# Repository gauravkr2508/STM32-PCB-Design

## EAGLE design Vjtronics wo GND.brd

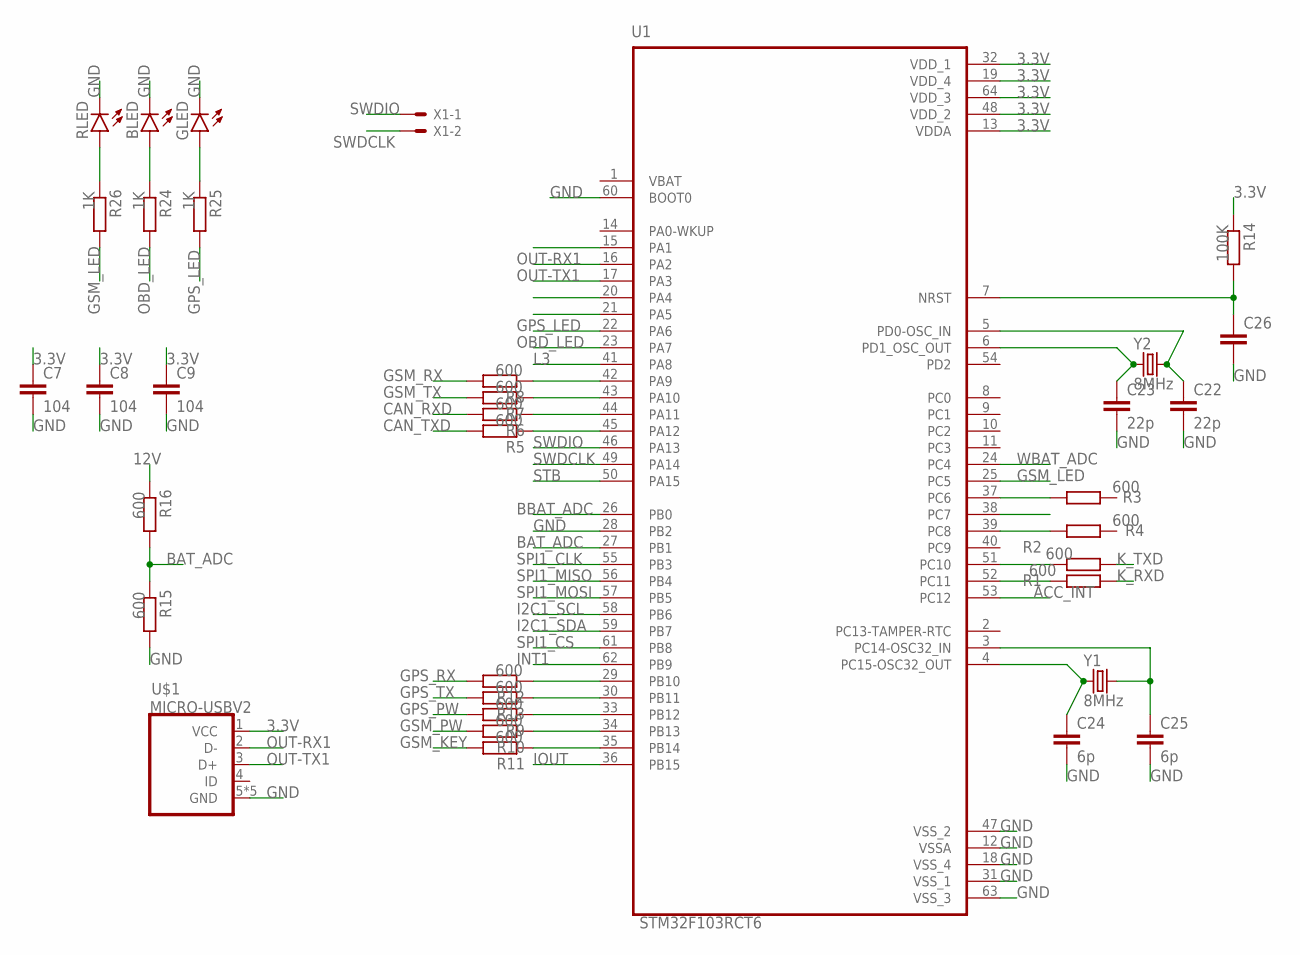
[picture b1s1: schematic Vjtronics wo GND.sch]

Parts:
BLED: LEDCHIPLED_0805; CHIPLED_0805
C7, C8, C9: 104; C0805
C22, C23: 22p; C0805
C24, C25: 6p; C0805
C26: C-EUC0805; C0805
GLED: LEDCHIPLED_0805; CHIPLED_0805
R1, R2, R3, R4, R5, R6, R7, R8, R9, R10, R11, R12, R13, R15, R16: 600; M0805
R14: 100K; M0805
R24, R25, R26: 1K; M0805
RLED: LEDCHIPLED_0805; CHIPLED_0805
U1: STM32F103RCT6; QFP50P1200X1200X160-64N
U$1: MICRO-USBV2; MICRO-USB-2
X1: 22-23-2021
Y1, Y2: 8MHz; CSM-7X-DU

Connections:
3.3V: C7.1, C8.1, C9.1, R14.1, U1.13 (VDDA), U1.19 (VDD_4), U1.32 (VDD_1), U1.48 (VDD_2), U1.64 (VDD_3), U$1.1 (VCC)
12V: R16.1
ACC_INT: U1.53 (PC12)
BAT_ADC: R15.1, R16.2, U1.27 (PB1)
BBAT_ADC: U1.26 (PB0)
CAN_RXD: R6.2
CAN_TXD: R5.2
GND: BLED.C, C7.2, C8.2, C9.2, C22.2, C23.2, C24.2, C25.2, C26.2, GLED.C, R15.2, RLED.C, U1.12 (VSSA), U1.18 (VSS_4), U1.28 (PB2), U1.31 (VSS_1), U1.47 (VSS_2), U1.60 (BOOT0), U1.63 (VSS_3), U$1.5 (GND), U$1.P$1 (GND), U$1.P$2 (GND), U$1.P$3 (GND), U$1.P$4 (GND)
GPS_LED: R25.2, U1.22 (PA6)
GPS_PW: R9.2
GPS_RX: R12.2
GPS_TX: R13.2
GSM_KEY: R11.2
GSM_LED: R26.2, U1.25 (PC5)
GSM_PW: R10.2
GSM_RX: R8.2
GSM_TX: R7.2
I2C1_SCL: U1.58 (PB6)
I2C1_SDA: U1.59 (PB7)
INT1: U1.62 (PB9)
IOUT: U1.36 (PB15)
K_RXD: R1.1
K_TXD: R2.1
L3: U1.41 (PA8)
unnamed: R13.1, U1.30 (PB11)
unnamed: R5.1, U1.45 (PA12)
unnamed: R6.1, U1.44 (PA11)
unnamed: R7.1, U1.43 (PA10)
unnamed: R8.1, U1.42 (PA9)
unnamed: R1.2, U1.52 (PC11)
unnamed: R2.2, U1.51 (PC10)
unnamed: R12.1, U1.29 (PB10)
unnamed: R4.2, U1.39 (PC8)
unnamed: R3.2, U1.37 (PC6)
unnamed: R11.1, U1.35 (PB14)
unnamed: R10.1, U1.34 (PB13)
unnamed: R9.1, U1.33 (PB12)
unnamed: C23.1, U1.6 (PD1_OSC_OUT), Y2.1
unnamed: C26.1, R14.2, U1.7 (NRST)
unnamed: C22.1, U1.5 (PD0-OSC_IN), Y2.2
unnamed: C24.1, U1.4 (PC15-OSC32_OUT), Y1.1
unnamed: C25.1, U1.3 (PC14-OSC32_IN), Y1.2
unnamed: R26.1, RLED.A
unnamed: BLED.A, R24.1
unnamed: GLED.A, R25.1
OBD_LED: R24.2, U1.23 (PA7)
OUT-RX1: U1.16 (PA2), U$1.2 (D-)
OUT-TX1: U1.17 (PA3), U$1.3 (D+)
SPI1_CLK: U1.55 (PB3)
SPI1_CS: U1.61 (PB8)
SPI1_MISO: U1.56 (PB4)
SPI1_MOSI: U1.57 (PB5)
STB: U1.50 (PA15)
SWDCLK: U1.49 (PA14), X1.2
SWDIO: U1.46 (PA13), X1.1
WBAT_ADC: U1.24 (PC4)

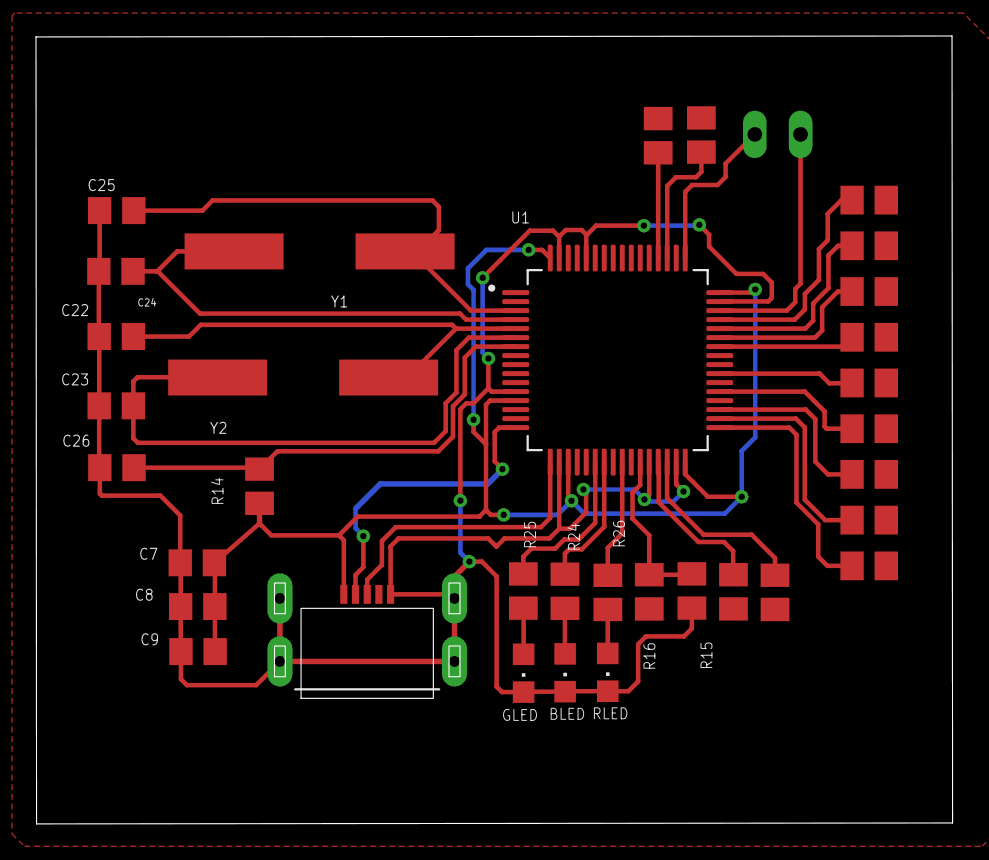
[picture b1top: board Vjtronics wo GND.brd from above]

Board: 2 copper layers, 50.9 x 43.8 mm, 35 parts (1 on the bottom side), 31 nets.
